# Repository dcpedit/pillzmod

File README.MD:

# Pillz Mod for the Kinesis Advantage/Contoured

This project replaces my two previous forks ([kinesismod](https://github.com/dcpedit/kinesismod) and [kint](https://github.com/dcpedit/kint)) for adding Blackpill support to the Kinesis keyboard.  I've decided to merge all the features into a single PCB, add optional thumb cluster PCBs as part of the kit, and renamed the project to avoid confusion.  Below is a list of supported features.

* Supports Blackpill development board running QMK/Vial
* Supports Pill Bug wireless Bluetooth development board running ZMK
* Optional reversible thumb cluster PCB for left/right sides.  (Maintains original matrix wiring)
* 2u stabilizer support on thumb cluster

## "Pro" PCB Features

* Supports devlopment board with Pro-Micro footprint (Elite-C, Elite-Pi, Nice!Nano)
* Header for connecting up to 3 foot-pedals
* Piezo audio buzzer
* Header for extra data pin (Elite-C only)

## Attribution

Credit goes to the following people for doing all the initial development on replacment PCBs for the Kinesis:
 * Aaron Silman's [kinesismod project](https://gitlab.com/Silman/kinesismod.git) ([blog](https://silman.io/project/kinesis_mod/))
 * Michael Stapelberg's [KinT project](https://github.com/kinx-project/kint) ([blog](https://michael.stapelberg.ch/posts/2020-07-09-kint-kinesis-keyboard-controller/))
 * Dmitry Nosachev's [Kin80 project](https://github.com/DmNosachev/kin80)

## Ordering PCBs from JLCPCB

The files needed for https://jlcpcb.com are located in the production folders:
* Choose `pcb-pro/production` or `pcb/production` 
* `thumb-pcb/production`

Once uploaded, you place the order with the selected default options.  You can optionally change the solder mask color, which changes the final color of your PCB.

## Main PCB build guide
### Components
| Position | Description | Qty | Notes |
| -------- | ----------- | --- | ----- |
| J1-J4    | Molex 39-53-2135 | 2 - 6  | [Link](https://octopart.com/39-53-2135-molex-7670149?r=sp)
| J3-J4    | Molex 39-53-2134 | 0 - 2  | Contoured only, [Link](https://octopart.com/search?q=Molex+39-53-2134)
| U1       | Header pins (1x20) | 2 | Should come with dev board
| U1       | Headers (1x20) | 2 | To socket your dev board
| D1-D4    | 1.8mm LED | 4 | [Amazon](https://a.co/d/90uynIs)
| R1-R4    | 10k resistor | 4 | Affects LED brightness. Smaller = brighter |
|          | USB-C panel mount | 1 | [AliExpress](https://www.aliexpress.us/item/3256806463941289.html?spm=a2g0o.order_list.order_list_main.43.18a31802pDYB6d&gatewayAdapt=glo2usa), [Amazon](https://a.co/d/cRoqHqx)

### Blackpill Components
| Position | Description | Qty | Notes |
| -------- | ----------- | --- | ----- |
| U1       | Blackpill (STM32F411) | 1 | [WeAct Store](https://www.aliexpress.com/store/1101545918?spm=a2g0o.order_list.order_list_main.2.18a31802pDYB6d)

#### -or- Pill Bug for wireless build

| Description | Qty | Notes |
| ----------- | --- | ----- |
| Pill Bug | 1 | [MechWild Store](https://mechwild.com/product/pillbug/)
| 3.7V battery | 1 | [2000mAh](https://a.co/d/dVUdHxi)
| Power button | 1 | Optional, [10mm](https://a.co/d/i33uBM0) or [19mm](https://a.co/d/fYN6ZX5)

### Additional "Pro" Components

| Position | Description | Qty | Notes |
| -------- | ----------- | --- | ----- |
| U1       | Elite-C/Elite-Pi | 1 |
|          | 3.7V battery | 1 | [2000mAh](https://a.co/d/dVUdHxi)
| U2       | 74HC595      | 1 | [Amazon](https://a.co/d/eLX9kOY)
| U2       | 16-pin IC socket | 1 | [Amazon](https://a.co/d/5EaFAHo)
| D6-D8    | 1n4148 Diode | 3 | [Link](https://www.mouser.com/ProductDetail/512-1N4148TR)
| BZ1      | Piezo Buzzer | 1 | [Link](https://www.digikey.com/en/products/detail/tdk-corporation/PS1240P02BT/935924)
| SW1      | Reset button | 1 | [Link](https://www2.mouser.com/ProductDetail/Alps-Alpine/SKQGAEE010?qs=N5Jky1br14PyTRvcw7F3eQ%3D%3D)
| R5-R19   | 10k Resistor | 15| AVR/Elite-C Only [Link](https://www.mouser.com/ProductDetail/YAGEO/MFR-12FTF52-10K?qs=oAGoVhmvjhzLlUYKKBtdYQ%3D%3D), [Link](https://mou.sr/3xgqcNf)

#### -or- Nice!Nano for wireless build

| Description | Qty | Notes |
| ----------- | --- | ----- |
| Nice!Nano    | 1 | [Website](https://nicekeyboards.com/nice-nano/)
| 3.7V battery | 1 | [2000mAh](https://a.co/d/dVUdHxi)
| Power button | 1 | Optional, [10mm](https://a.co/d/i33uBM0) or [19mm](https://a.co/d/fYN6ZX5)

### Instructions

_NOTE: If you're using a battery that's larger than 500mAh, then bridge the charge boost jumper labeled JP1 with some solder.  This will increases the max charge rate from 100mA to 500mA. Doing this for small batteries (<500mAh) may cause explosions._

All components go on the side with the silkscreen labels (rectangles) EXCEPT for the LEDs.  First solder the header pins onto your development board, and the header sockets onto the PCB.  I prefer to use Mill-Max 310 series sockets because the pins are thin.  Then solder in the LED resistors, but NOT the actual LEDs yet.  The resistors can be SMD or through hole.

For a wireless build, you can now solder the battery wires/connector to the board.  Make sure the positive wire goes into "BAT+", and the negative wire goes into "BAT-".  If you're using a power button, make sure to wire it inline along the BAT+ wire so that it essentially opens and closes the circuit.

Insert your development board into the sockets on the PCB.

For the Molex connectors, I find that it's more convient to desolder the ones on the original PCB so that I don't have to purchase new ones.  Solder the connectors onto the PCB.

Flip the PCB over and insert the LEDs on the side of the PCB with no other components.  Make sure the short leg goes into the square pad, and bend the legs so that they stay in place.  Screw the PCB back into the keyboard case, making sure the LEDs are lined up with the existing case holes.  You can also adjust the height of the LED to move them closer to the status window if you'd like.  Once you're satisfied with the position of the LEDs, you can then solder them in place while the PCB is still mounted.

Lastly, plug the USB-C panel mount cable to into the development board, and secure the other end to the hole in the case.

### "Pro" Additional Instructions

The components required for this build and their position will depend on the development board you're using.  For example, pull-down resistors R5-R19 are only needed for AVR chips (Pro-Micro, Elite-C) since they don't support internal pull-downs for the row inputs.  Use the image below as a guide.

The Elite-C has an extra B0 pin that is broken out into the J10 pins.  You can use this to drive other components if you choose (ie. RGB strip, Solenoid)

* Pin 1 (square pad) - VCC
* Pin 2 - B0
* Pin 3 - GND

The J9 pins are for foot pedals and have the following assignment:

* Pin 1 (square pad) - Col6
* Pin 2 - Row0
* Pin 3 - Row1
* Pin 4 - Row2

Diodes D6-D8 are connected to the rows, so no additional diodes are needed in the pedals/switches.

### "Pro" Nice!Nano Additional Instructions

Mill-Max 310 sockets are recommended for socketing the Nice!Nano because thin pins are required for connecting the extra 3 pins in the middle.

The Nice!Nano is one pin short of supporting all 4 status lights on the Advantage.  If you want to utilize the unused numpad status LED as a power indicator, go ahead and short JP1 with some solder.

## Thumb cluster PCB build guide

The wiring for the thumb cluster (a.k.a. matrix wiring) has not been altered from original, so theoretically, they can be used in conjunction with any Kinesis PCB, including the stock one.

The PCB is also reversible, so you don't have to place separate orders for a "left" version and a "right" version.

### Components

| Description | Qty | Notes |
| ----------- | --- | ----- |
| 1N4148 SOD-123 diode | 12 | [Amazon](https://a.co/d/gsv8bGT)
| MX switch | 12 | Can desolder and reuse
| 2u screw-in stabilizer | 4 | [Link](https://divinikey.com/products/durock-v2-stabilizers-screw-in)
| Cable connector (1x10) | 4 | 2.54mm pitch (eg KF2510)
| Ribbon cable | 2 | >= 50mm length

### Instructions

You will need two PCBs for the thumb cluster, but since they're reversible, you will need to read the silkscreen to see if it's the left or right cluster.

First step is to solder all the 1N4148 diodes.  Orientation matters, so make sure the line on the diode faces same direction as the thicker white line on the PCB.  Place a dab of solder on ONE of the two diode pads.  Drop the diode into position (double checking the orientation), hold the diode in place with tweezers, and melt the solder you just added to the pad so that diode is held in place.  Now add solder to the opposite pad, thus holding the other diode leg in place.  Repeat for all the other diodes.

The connector for the ribbon cable can now be soldered onto the PCB, and will be on the same side as the diodes.  The pin pitch is 2.54mm, so any compatible connector/cable will work here.

Install the 2u stabilizers onto the PCB.

Now solder in your MX switches.  If you're reusing the original switches, desolder them from the original PCB, and remove the diode from inside the switch housing.  Using a switch opener will make this task much easier.

Mount the thumb clusters onto the keyboard and connect the ribbon cables.

## QMK firmware for "Pro"

* `firmware/pro_qmk_avr_default.bin`
* `firmware/pro_qmk_rp2040_default.uf2`

QMK source: https://github.com/dcpedit/qmk_firmware/tree/pillzmod/keyboards/dcpedit/pillzmod

## Vial firmware for Blackpill

* `firmware/blackpill_vial.bin`
* `firmware/dcpedit_kint_bp_vial_6layers.bin`

Source: https://github.com/dcpedit/vial-qmk/tree/pillzmod/keyboards/dcpedit/pillzmod

Remap keys: https://vial.rocks/

### Flashing firmware under Linux
The file firmware/dcpedit_kint_bp_vial_6layers.bin (or other) can simply be flashed to the Blackpill using the dfu-util. The dfu-util tool requires root privileges if settings are not accessible by the user.

Connect Blackpill to your Linux PC via USB C cable and start unit in DFU mode by holding bootp button and pressing reset button. Wait a second and release the bootp button.

Check the DFU devices by running
```
dfu-util -l
```
The Blackpill device should be visible.

Write the firmware to the device with
```
dfu-util -d 0483:df11 -a 0 -s 0x08000000 -D [PATH TO kint]/firmware/dcpedit_kint_bp_vial_6layers.bin
```

## Vial firmware for "Pro"

* `firmware/pro_vial_avr.hex`

Source: https://github.com/dcpedit/vial-qmk/tree/pillzmod/keyboards/dcpedit/pillzmod
(You will need to clone the entire branch since I had to make a core code change in `spi_master.c`)

## ZMK firmware for Pill Bug

* `firmware/zmk_default.uf2` - Default keymap
* `firmware/zmk_custom.uf2` - Support for up to 6 layers
* `firmware/zmk_reset.uf2` - Resets PillBug board for BT connectivity issue on MacOS      
* `firmware/zmk_studio.uf2` - Studio compatible (Progrm + Esc to unlock)

Source: https://github.com/dcpedit/zmk/tree/pillzmod/app/boards/shields/pillzmod

### Bluetooth with ZMK

The ZMK firmware has mappings for performing system tasks. By default there are 4 Bluetooth pairings saved to the keyboard but they do not switch automatically when adding new devices. So after you add the first device, you need to tell they keyboard to use Bluetooth slot 2 and so forth.
The keys to switch between are accessed by a different keyboard layer. This layer is opened by holding down the "Program" key at the very top right of the Kinesis and, while holding it, then clicking another key as follows:

* **Clear all saved Bluetooth profiles:** Program + F9
* **Bluetooth profile 1:** Program + F1
* **Bluetooth profile 2:** Program + F2
* **Bluetooth profile 3:** Program + F3
* **Bluetooth profile 4:** Program + F4
* **Enter bootloader mode (to upload UF2 files):** Program + - (the dash key just below program)

If you want to do a ZMK firmware build using GitHub actions, take a look at the following repository from keepitsimplejim:

https://github.com/keepitsimplejim/zmk-config-pillzmod-kinesis-adv

## ZMK firmware for "Pro" Nice!Nano

* `firmware/pro_zmk.uf2` - Default keymap
* `firmware/pro_zmk_studio.uf2` - Studio compatible (Progrm + Esc to unlock)

Source: https://github.com/dcpedit/zmk/tree/pillzmod/app/boards/shields/pillzmod_pro
Studio: https://zmk.studio/

## KiCad

All the PCBs were designed using KiCad, which is free and can be downloaded here: https://www.kicad.org/

For the thumb cluster PCB, I wasn't able to figure out how to have the left and right wiring co-exist without errors while sharing the same connector footprint.  My workaround was to first change the connector's reference designator to "J1", update the PCB from schematic, and wire up the left side.  Then I changed the reference designator to "J2", updated the PCB from schematic again, and wired up the right side.

If there are any KiCad experts out there that know of a more elegant solution, please let me know.

The production JLCPCB files are all generated with Fabrication Toolkit: https://github.com/bennymeg/Fabrication-Toolkit

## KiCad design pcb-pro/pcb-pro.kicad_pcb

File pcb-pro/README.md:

# Pillz Mod Pro main PCB

Next image shows the mapping of keys to connectors and rows/columns:

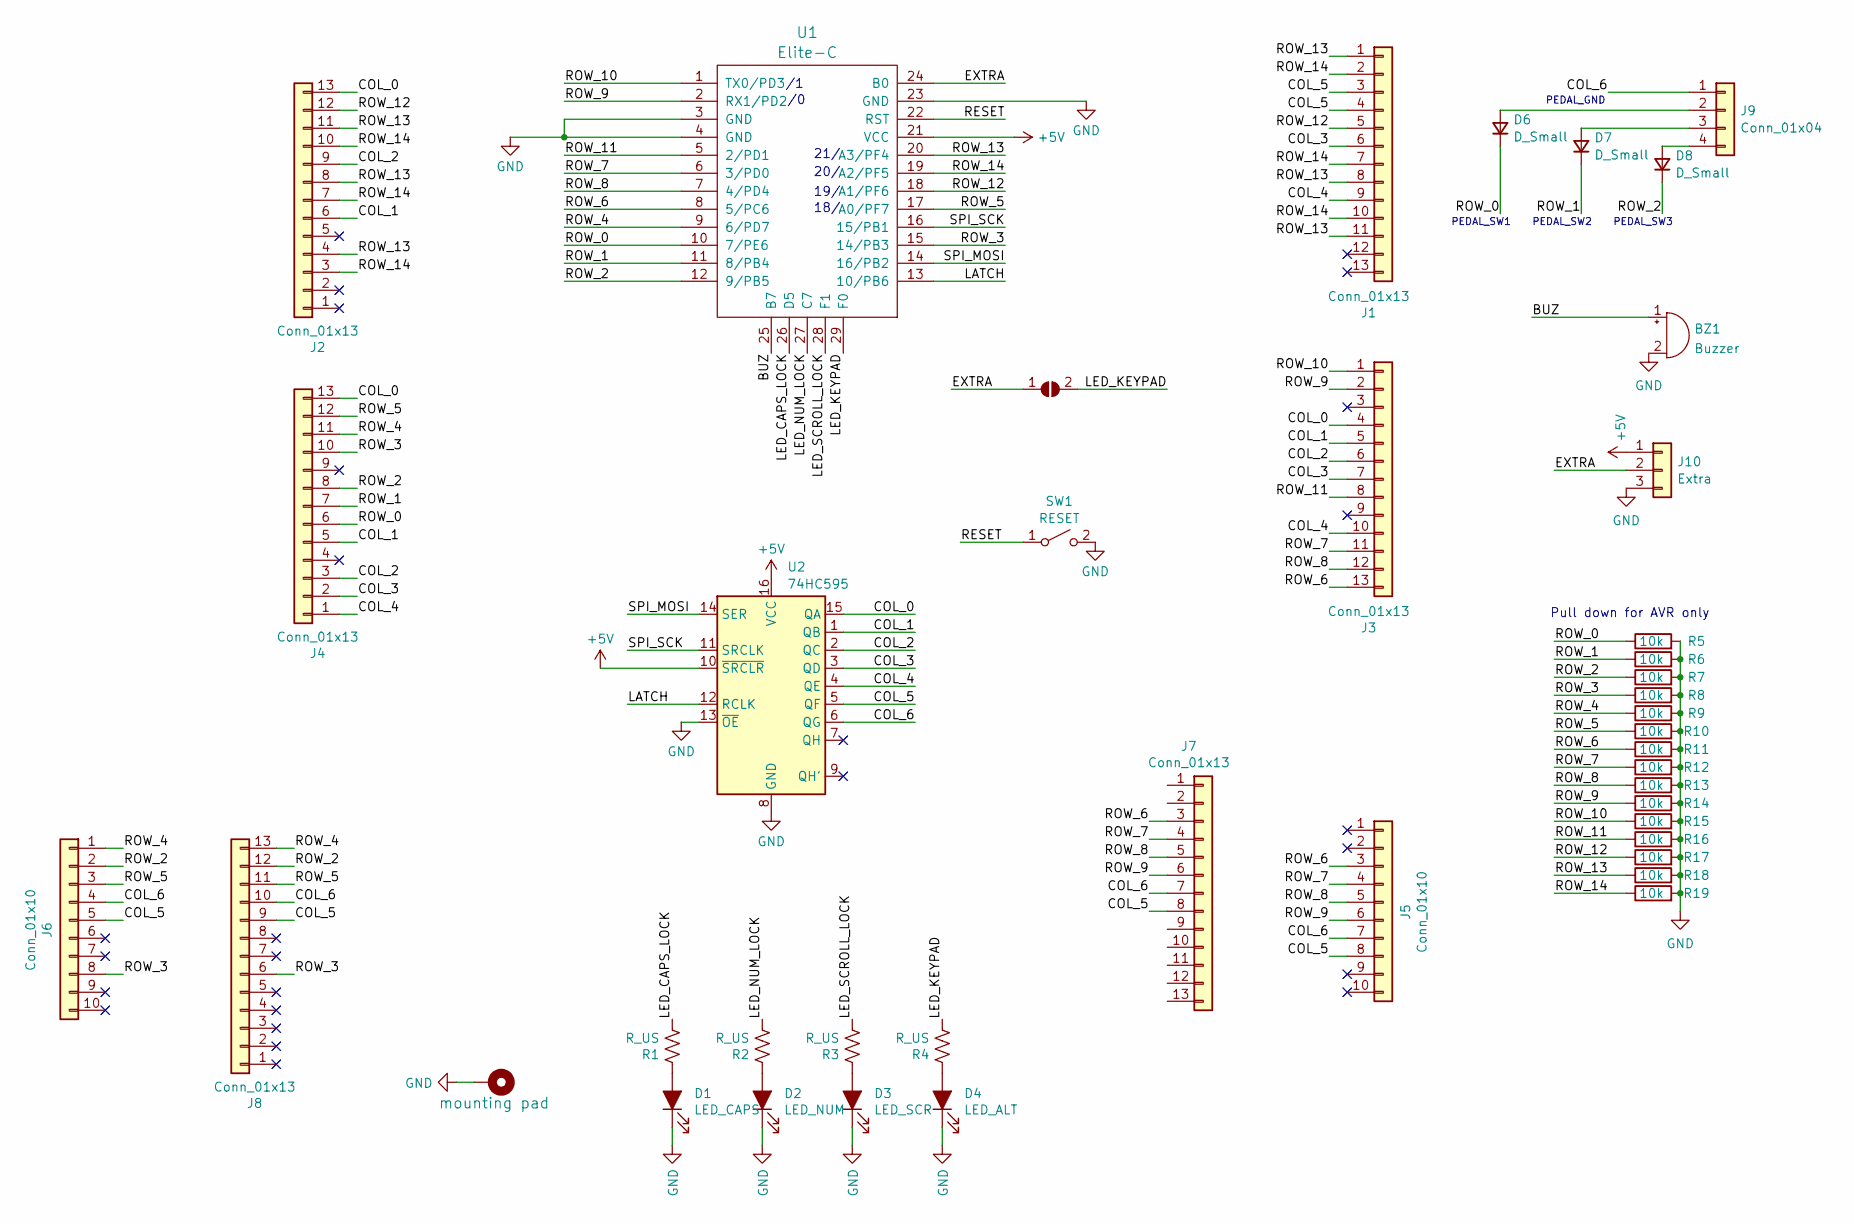
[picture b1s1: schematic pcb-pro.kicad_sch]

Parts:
BZ1: Buzzer
D1: LED_CAPS; LED_D3.0mm
D2: LED_NUM; LED_D3.0mm
D3: LED_SCR; LED_D3.0mm
D4: LED_ALT; LED_D3.0mm
D6, D7, D8: D_Small
H1: mounting pad; MountingHole_4.3mm_M4_Pad
J1, J2, J7, J8: Conn_01x13; Molex_0039532135
J3, J4: Conn_01x13; Molex_039532134
J5, J6: Conn_01x10; Pin_Header_Straight_1x10_Pitch2.54mm
J9: Conn_01x04
J10: Extra
JP1: SolderJumper_2_Open; SolderJumper-2_P1.3mm_Open_RoundedPad1.0x1.5mm
R1, R2, R3, R4: R_US; R_Axial_DIN0204_L3.6mm_D1.6mm_P5.08mm_Horizontal
R5, R6, R7, R8, R9, R10, R11, R12, R13, R14, R15, R16, R17, R18, R19: 10k
SW1: RESET
U1: Elite-C
U2: 74HC595

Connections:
+5V: J10.1, U1.21 (VCC), U2.10 (~SRCLR), U2.16 (VCC)
/BUZ: BZ1.1 (-), U1.25 (B7)
/COL_0: J2.13, J3.4, J4.13, U2.15 (QA)
/COL_1: J2.6, J3.5, J4.5, U2.1 (QB)
/COL_2: J2.9, J3.6, J4.3, U2.2 (QC)
/COL_3: J1.6, J3.7, J4.2, U2.3 (QD)
/COL_4: J1.9, J3.10, J4.1, U2.4 (QE)
/COL_5: J1.3, J1.4, J5.8, J6.5, J7.8, J8.9, U2.5 (QF)
/COL_6: J5.7, J6.4, J7.7, J8.10, J9.1, U2.6 (QG)
/EXTRA: J10.2, JP1.1 (A), U1.24 (B0)
/LATCH: U1.13 (10/PB6), U2.12 (RCLK)
/LED_CAPS_LOCK: R1.2, U1.26 (D5)
/LED_KEYPAD: JP1.2 (B), R4.2, U1.29 (F0)
/LED_NUM_LOCK: R2.2, U1.27 (C7)
/LED_SCROLL_LOCK: R3.2, U1.28 (F1)
/RESET: SW1.1 (A), U1.22 (RST)
/ROW_0: D6.1 (K), J4.6, R5.1, U1.10 (7/PE6)
/ROW_1: D7.1 (K), J4.7, R6.1, U1.11 (8/PB4)
/ROW_2: D8.1 (K), J4.8, J6.2, J8.12, R7.1, U1.12 (9/PB5)
/ROW_3: J4.10, J6.8, J8.6, R8.1, U1.15 (14/PB3)
/ROW_4: J4.11, J6.1, J8.13, R9.1, U1.9 (6/PD7)
/ROW_5: J4.12, J6.3, J8.11, R10.1, U1.17 (A0/PF7)
/ROW_6: J3.13, J5.3, J7.3, R11.1, U1.8 (5/PC6)
/ROW_7: J3.11, J5.4, J7.4, R12.1, U1.6 (3/PD0)
/ROW_8: J3.12, J5.5, J7.5, R13.1, U1.7 (4/PD4)
/ROW_9: J3.2, J5.6, J7.6, R14.1, U1.2 (RX1/PD2)
/ROW_10: J3.1, R15.1, U1.1 (TX0/PD3)
/ROW_11: J3.8, R16.1, U1.5 (2/PD1)
/ROW_12: J1.5, J2.12, R17.1, U1.18 (A1/PF6)
/ROW_13: J1.1, J1.8, J1.11, J2.4, J2.8, J2.11, R18.1, U1.20 (A3/PF4)
/ROW_14: J1.2, J1.7, J1.10, J2.3, J2.7, J2.10, R19.1, U1.19 (A2/PF5)
/SPI_MOSI: U1.14 (16/PB2), U2.14 (SER)
/SPI_SCK: U1.16 (15/PB1), U2.11 (SRCLK)
GND: BZ1.2 (+), D1.1 (K), D2.1 (K), D3.1 (K), D4.1 (K), H1.1, J10.3, R5.2, R6.2, R7.2, R8.2, R9.2, R10.2, R11.2, R12.2, R13.2, R14.2, R15.2, R16.2, R17.2, R18.2, R19.2, SW1.2 (B), U1.3 (GND), U1.4 (GND), U1.23 (GND), U2.8 (GND), U2.13 (~OE)
unnamed: D1.2 (A), R1.1
unnamed: D2.2 (A), R2.1
unnamed: D3.2 (A), R3.1
unnamed: D4.2 (A), R4.1
unnamed: D6.2 (A), J9.2
unnamed: D7.2 (A), J9.3
unnamed: D8.2 (A), J9.4

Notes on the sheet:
Pull down for AVR only
18/
PEDAL_SW3
19/
20/
PEDAL_SW1
21/
PEDAL_GND
PEDAL_SW2

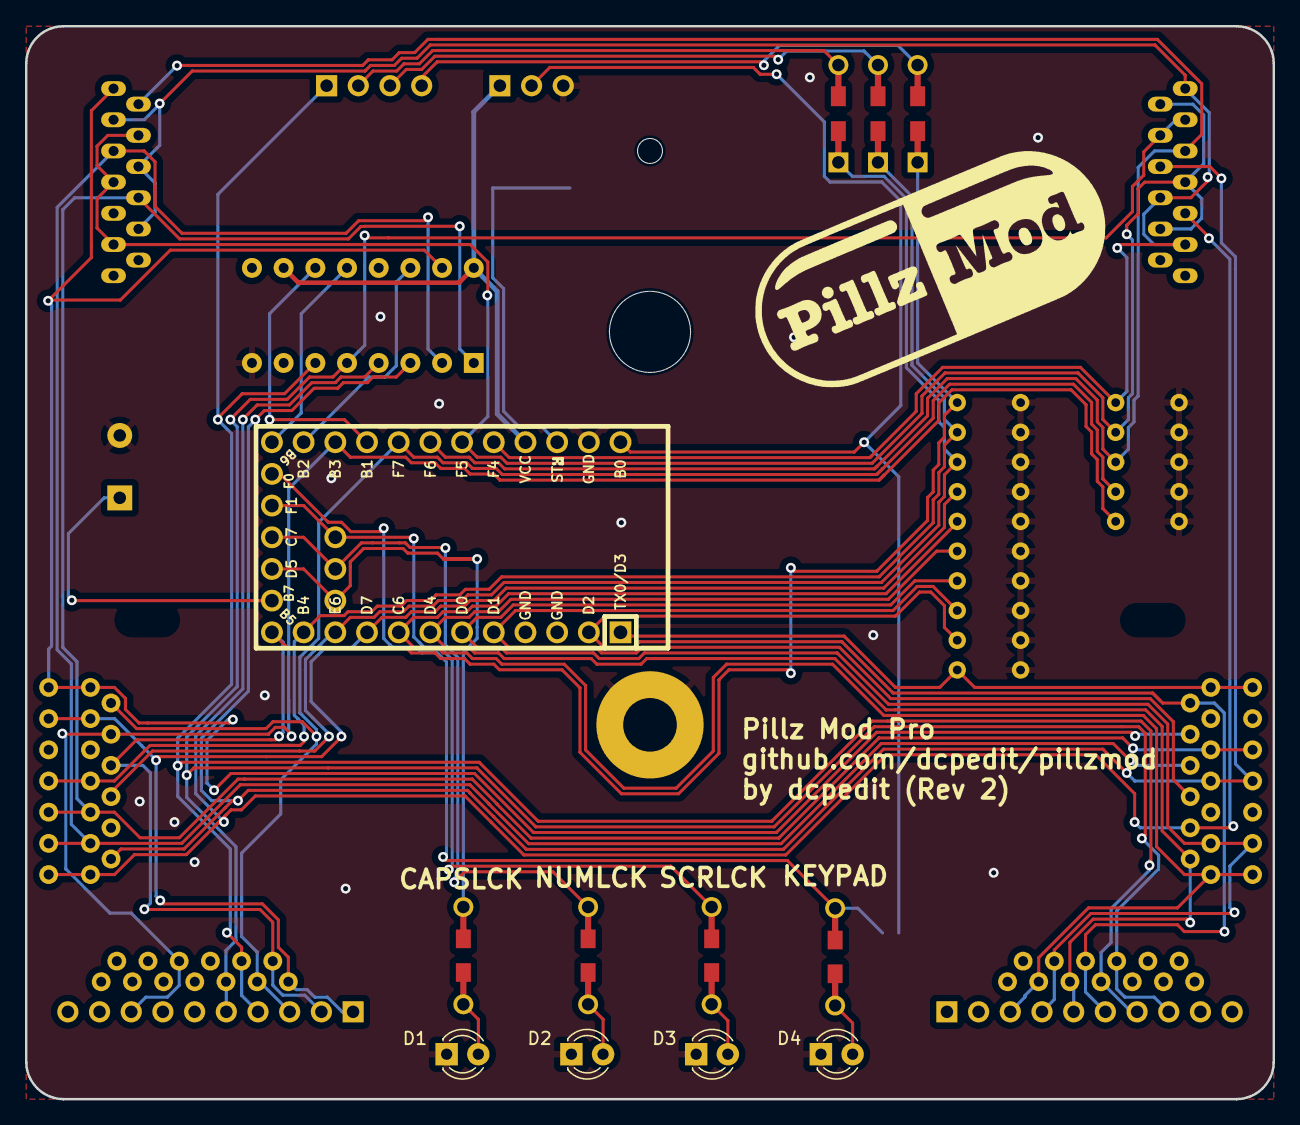
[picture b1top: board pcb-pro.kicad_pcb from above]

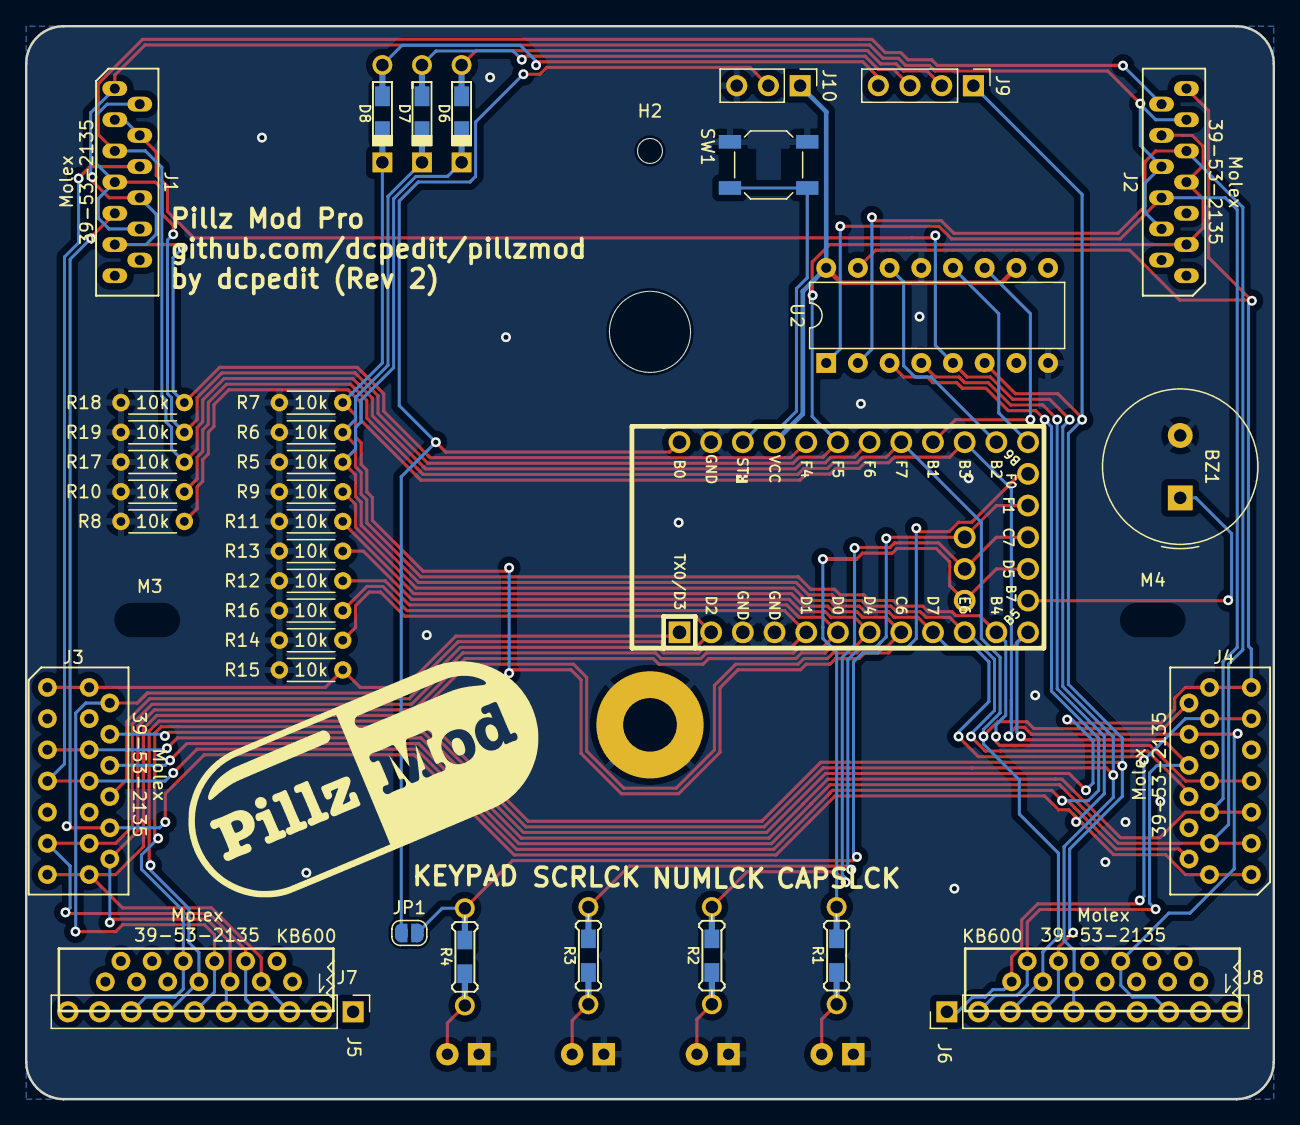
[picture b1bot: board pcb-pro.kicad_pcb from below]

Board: 2 copper layers, 100.0 x 86.0 mm, 46 parts (41 on the bottom side), 41 nets.

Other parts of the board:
H2: mounting pad; MountingHole_2mm
M1: MountingHole_6.4mm_M6
M3, M4: MountingHole_4.3mm_M4

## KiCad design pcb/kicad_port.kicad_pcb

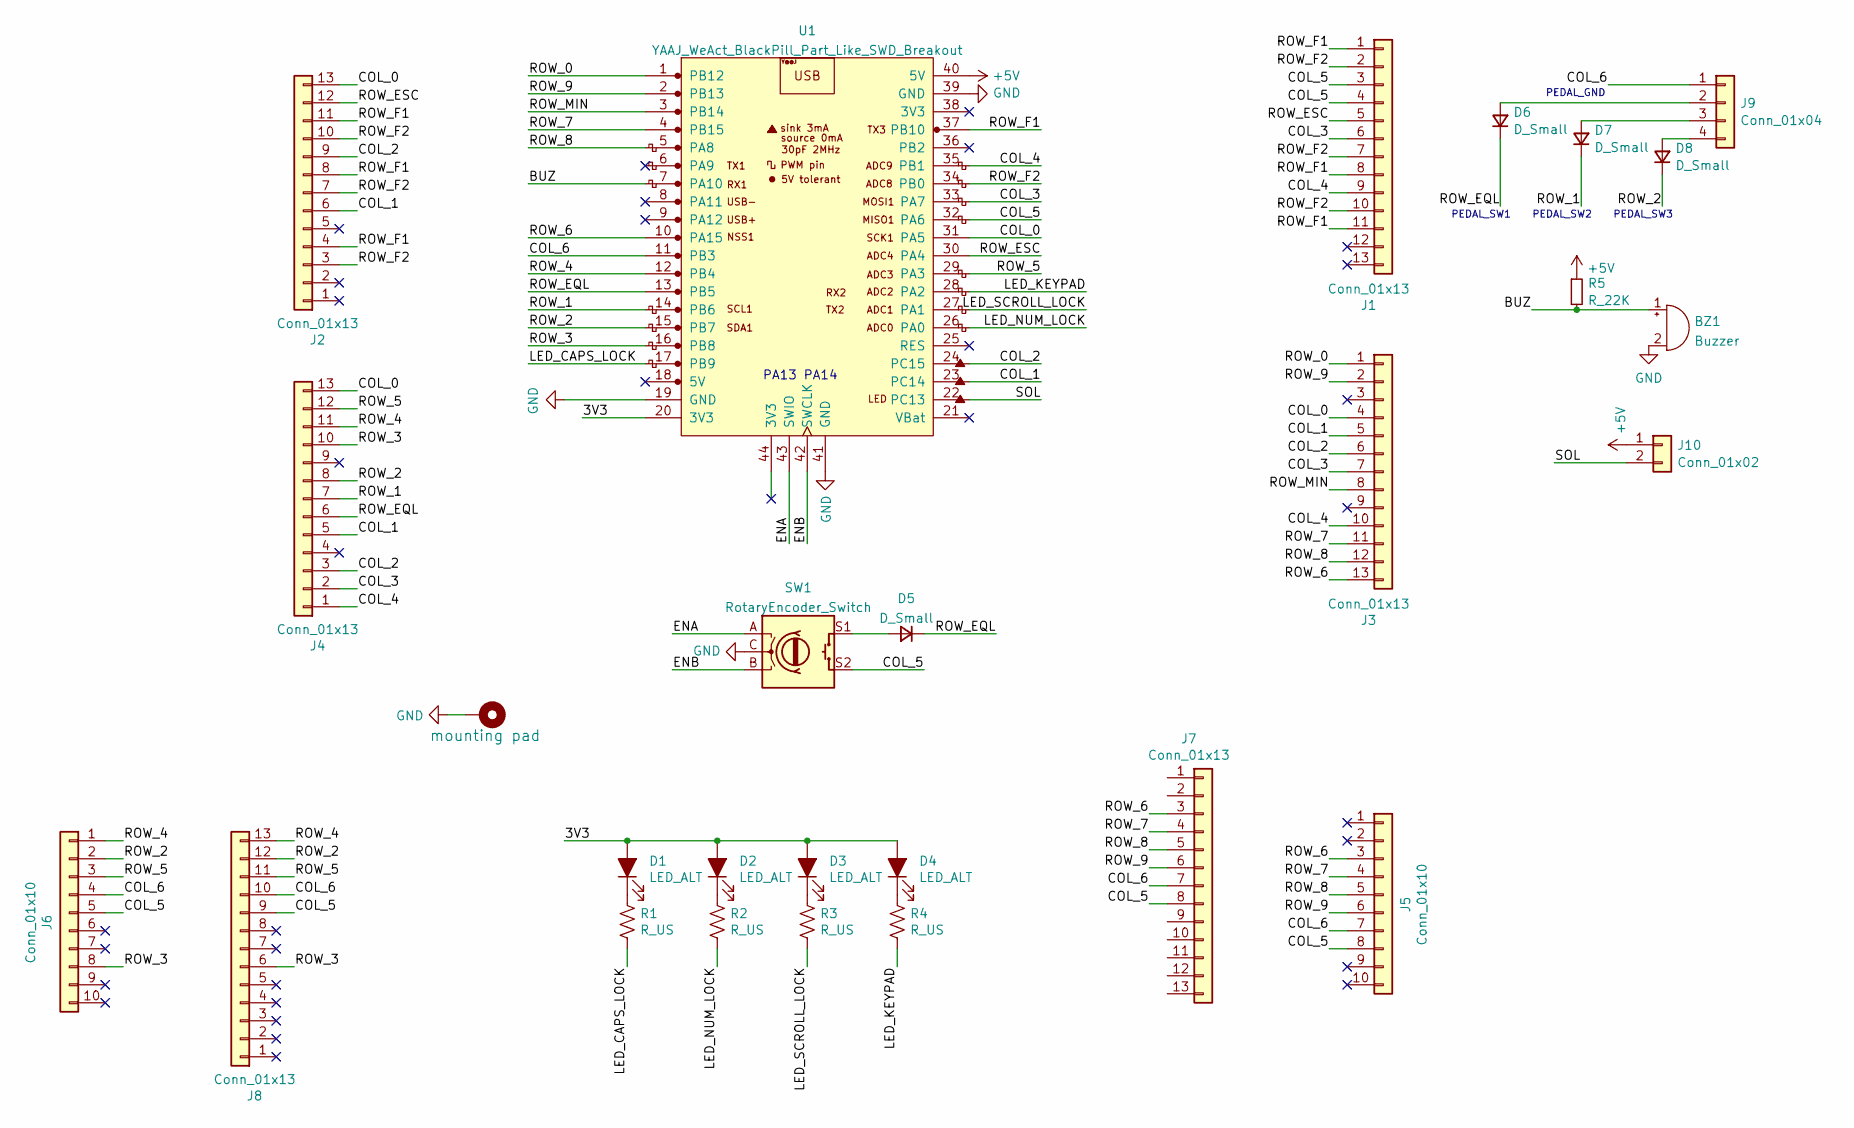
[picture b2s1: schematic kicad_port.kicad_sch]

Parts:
BZ1: Buzzer
D1, D2, D3, D4: LED_ALT; LED_D3.0mm
D5, D6, D7, D8: D_Small
H1: mounting pad; MountingHole_4.3mm_M4_Pad
J1, J2, J7, J8: Conn_01x13; Molex_0039532135
J3, J4: Conn_01x13; Molex_039532134
J5, J6: Conn_01x10; Pin_Header_Straight_1x10_Pitch2.54mm
J9: Conn_01x04
J10: Conn_01x02
R1, R2, R3, R4: R_US; R_Axial_DIN0204_L3.6mm_D1.6mm_P5.08mm_Horizontal
R5: R_22K; Resistor
SW1: RotaryEncoder_Switch
U1: YAAJ_WeAct_BlackPill_Part_Like_SWD_Breakout; YAAJ_WeAct_BlackPill_SWD_2

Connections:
+5V: J10.1, R5.1, U1.40 (5V)
/3V3: D1.2 (A), D2.2 (A), D3.2 (A), D4.2 (A), U1.20 (3V3)
/BUZ: BZ1.1 (-), R5.2, U1.7 (PA10)
/COL_0: J2.13, J3.4, J4.13, U1.31 (PA5)
/COL_1: J2.6, J3.5, J4.5, U1.23 (PC14)
/COL_2: J2.9, J3.6, J4.3, U1.24 (PC15)
/COL_3: J1.6, J3.7, J4.2, U1.33 (PA7)
/COL_4: J1.9, J3.10, J4.1, U1.35 (PB1)
/COL_5: J1.3, J1.4, J5.8, J6.5, J7.8, J8.9, SW1.S2, U1.32 (PA6)
/COL_6: J5.7, J6.4, J7.7, J8.10, J9.1, U1.11 (PB3)
/ENA: SW1.A, U1.43 (SWIO)
/ENB: SW1.B, U1.42 (SWCLK)
/LED_CAPS_LOCK: R1.2, U1.17 (PB9)
/LED_KEYPAD: R4.2, U1.28 (PA2)
/LED_NUM_LOCK: R2.2, U1.26 (PA0)
/LED_SCROLL_LOCK: R3.2, U1.27 (PA1)
/ROW_0: J3.1, U1.1 (PB12)
/ROW_1: D7.1 (K), J4.7, U1.14 (PB6)
/ROW_2: D8.1 (K), J4.8, J6.2, J8.12, U1.15 (PB7)
/ROW_3: J4.10, J6.8, J8.6, U1.16 (PB8)
/ROW_4: J4.11, J6.1, J8.13, U1.12 (PB4)
/ROW_5: J4.12, J6.3, J8.11, U1.29 (PA3)
/ROW_6: J3.13, J5.3, J7.3, U1.10 (PA15)
/ROW_7: J3.11, J5.4, J7.4, U1.4 (PB15)
/ROW_8: J3.12, J5.5, J7.5, U1.5 (PA8)
/ROW_9: J3.2, J5.6, J7.6, U1.2 (PB13)
/ROW_EQL: D5.1 (K), D6.1 (K), J4.6, U1.13 (PB5)
/ROW_ESC: J1.5, J2.12, U1.30 (PA4)
/ROW_F1: J1.1, J1.8, J1.11, J2.4, J2.8, J2.11, U1.37 (PB10)
/ROW_F2: J1.2, J1.7, J1.10, J2.3, J2.7, J2.10, U1.34 (PB0)
/ROW_MIN: J3.8, U1.3 (PB14)
/SOL: J10.2, U1.22 (PC13)
GND: BZ1.2 (+), H1.1, SW1.C, U1.19 (GND), U1.39 (GND), U1.41 (GND)
unnamed: D1.1 (K), R1.1
unnamed: D2.1 (K), R2.1
unnamed: D3.1 (K), R3.1
unnamed: D4.1 (K), R4.1
unnamed: D5.2 (A), SW1.S1
unnamed: D6.2 (A), J9.2
unnamed: D7.2 (A), J9.3
unnamed: D8.2 (A), J9.4

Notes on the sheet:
PA13 PA14
PEDAL_SW3
PEDAL_SW1
PEDAL_GND
PEDAL_SW2

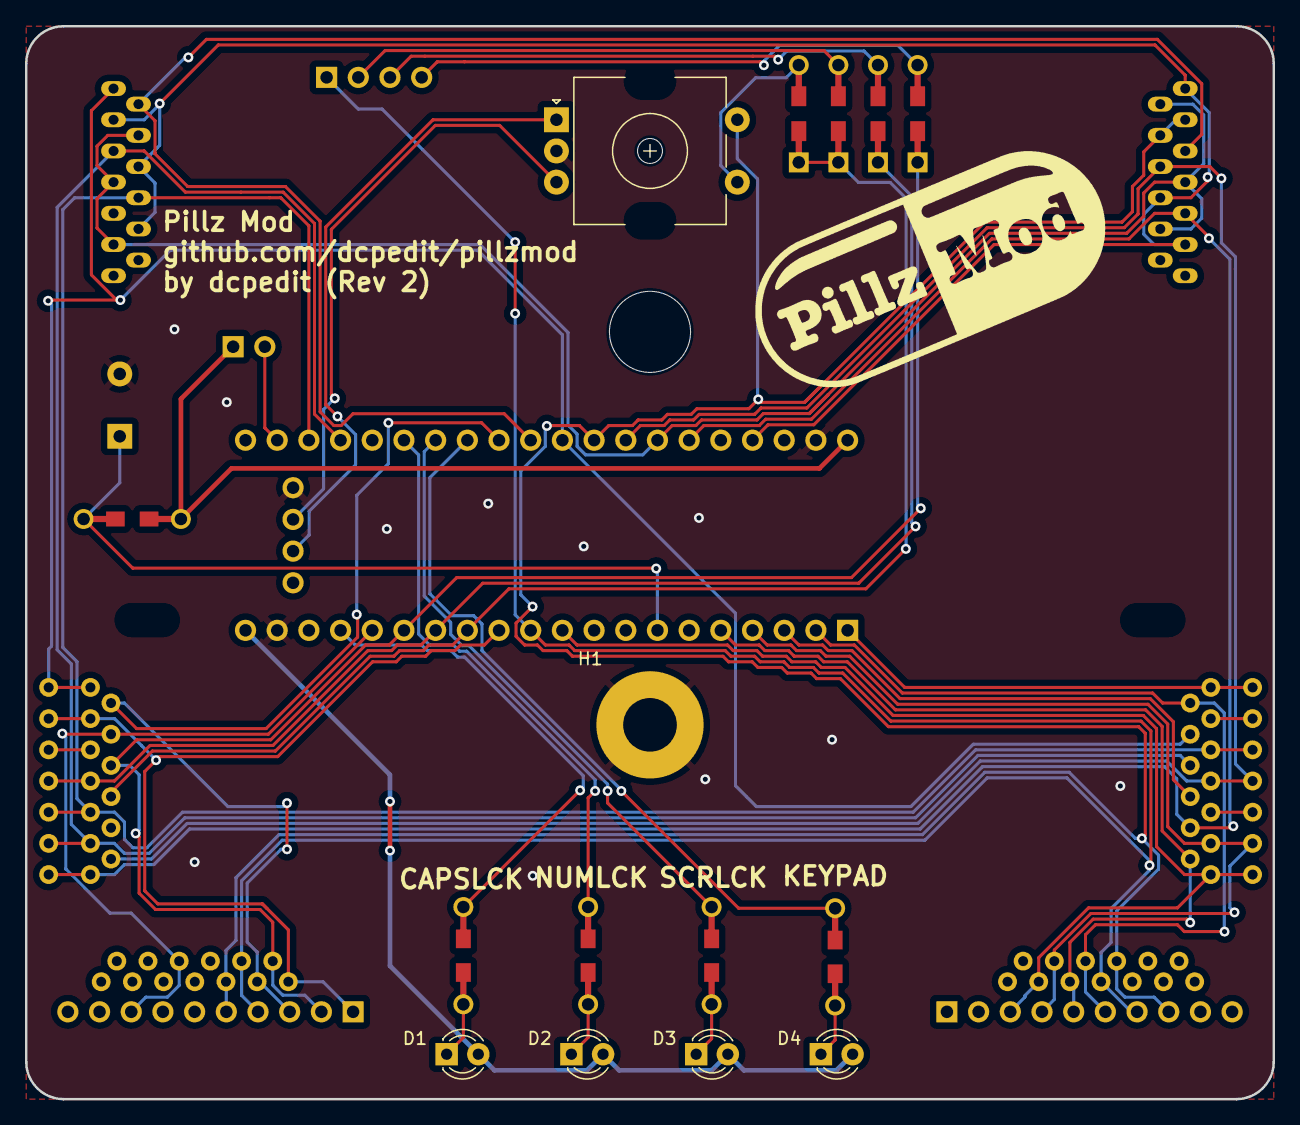
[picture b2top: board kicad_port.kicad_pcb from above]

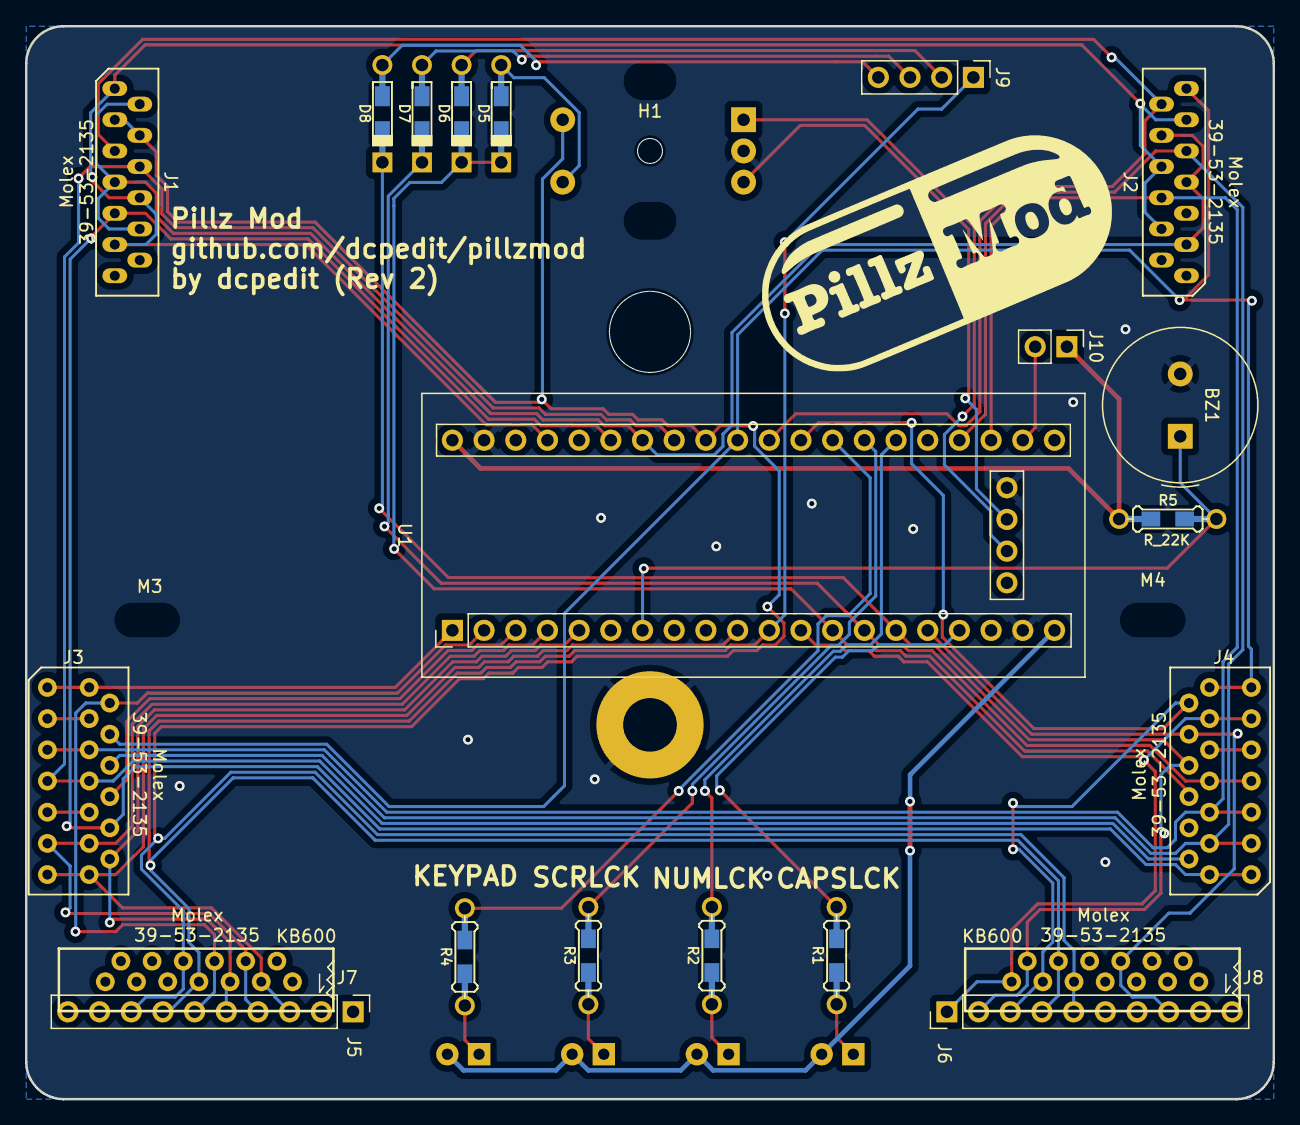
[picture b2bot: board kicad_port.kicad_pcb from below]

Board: 2 copper layers, 100.0 x 86.0 mm, 31 parts (25 on the bottom side), 41 nets.

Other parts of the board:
H1#2: mounting pad; MountingHole_2mm
M1: MountingHole_6.4mm_M6
M3, M4: MountingHole_4.3mm_M4

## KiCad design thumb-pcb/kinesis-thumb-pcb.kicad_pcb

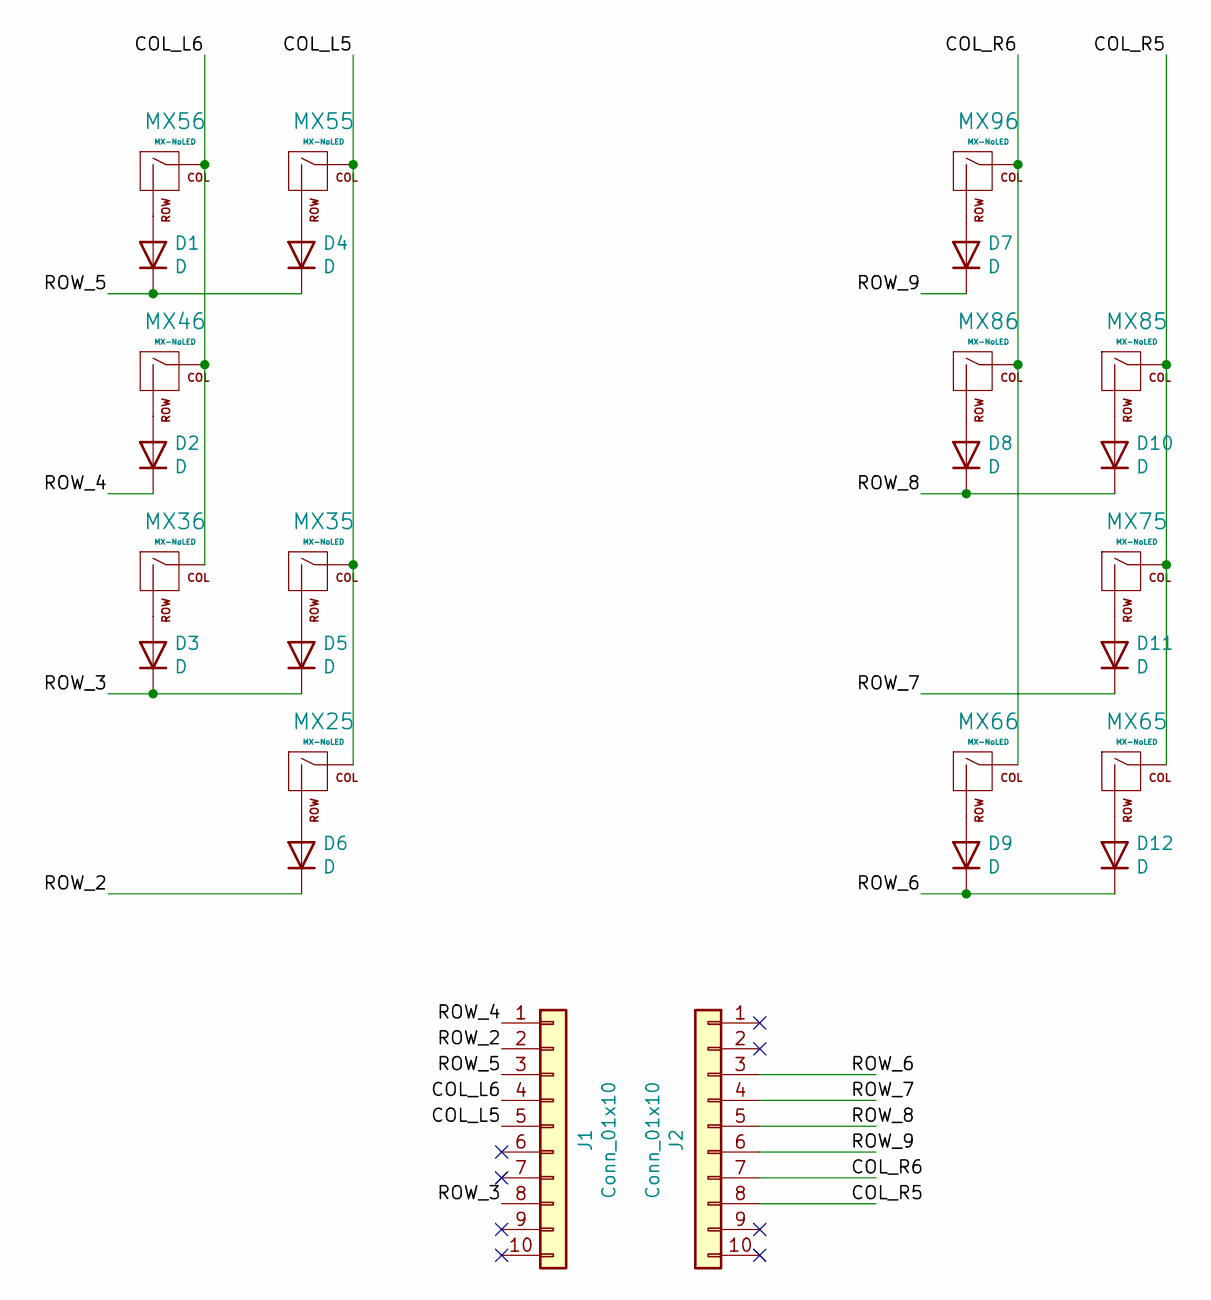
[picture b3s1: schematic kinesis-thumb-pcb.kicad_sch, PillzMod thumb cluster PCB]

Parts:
D1, D2, D3, D4, D5, D6, D7, D8, D9, D10, D11, D12: D; D_SOD-323_HandSoldering
J1, J2: Conn_01x10; Pin_Header_Straight_1x10_Pitch2.54mm
MX25, MX35, MX36, MX46, MX55, MX56, MX65, MX66, MX75, MX85, MX86, MX96: MX-NoLED

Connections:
/COL_L5: J1.5, MX25.1 (COL), MX35.1 (COL), MX55.1 (COL)
/COL_L6: J1.4, MX36.1 (COL), MX46.1 (COL), MX56.1 (COL)
/COL_R5: J2.8, MX65.1 (COL), MX75.1 (COL), MX85.1 (COL)
/COL_R6: J2.7, MX66.1 (COL), MX86.1 (COL), MX96.1 (COL)
/ROW_2: D6.1 (K), J1.2
/ROW_3: D3.1 (K), D5.1 (K), J1.8
/ROW_4: D2.1 (K), J1.1
/ROW_5: D1.1 (K), D4.1 (K), J1.3
/ROW_6: D9.1 (K), D12.1 (K), J2.3
/ROW_7: D11.1 (K), J2.4
/ROW_8: D8.1 (K), D10.1 (K), J2.5
/ROW_9: D7.1 (K), J2.6
unnamed: D1.2 (A), MX56.2 (ROW)
unnamed: D2.2 (A), MX46.2 (ROW)
unnamed: D3.2 (A), MX36.2 (ROW)
unnamed: D4.2 (A), MX55.2 (ROW)
unnamed: D5.2 (A), MX35.2 (ROW)
unnamed: D6.2 (A), MX25.2 (ROW)
unnamed: D7.2 (A), MX96.2 (ROW)
unnamed: D8.2 (A), MX86.2 (ROW)
unnamed: D9.2 (A), MX66.2 (ROW)
unnamed: D10.2 (A), MX85.2 (ROW)
unnamed: D11.2 (A), MX75.2 (ROW)
unnamed: D12.2 (A), MX65.2 (ROW)

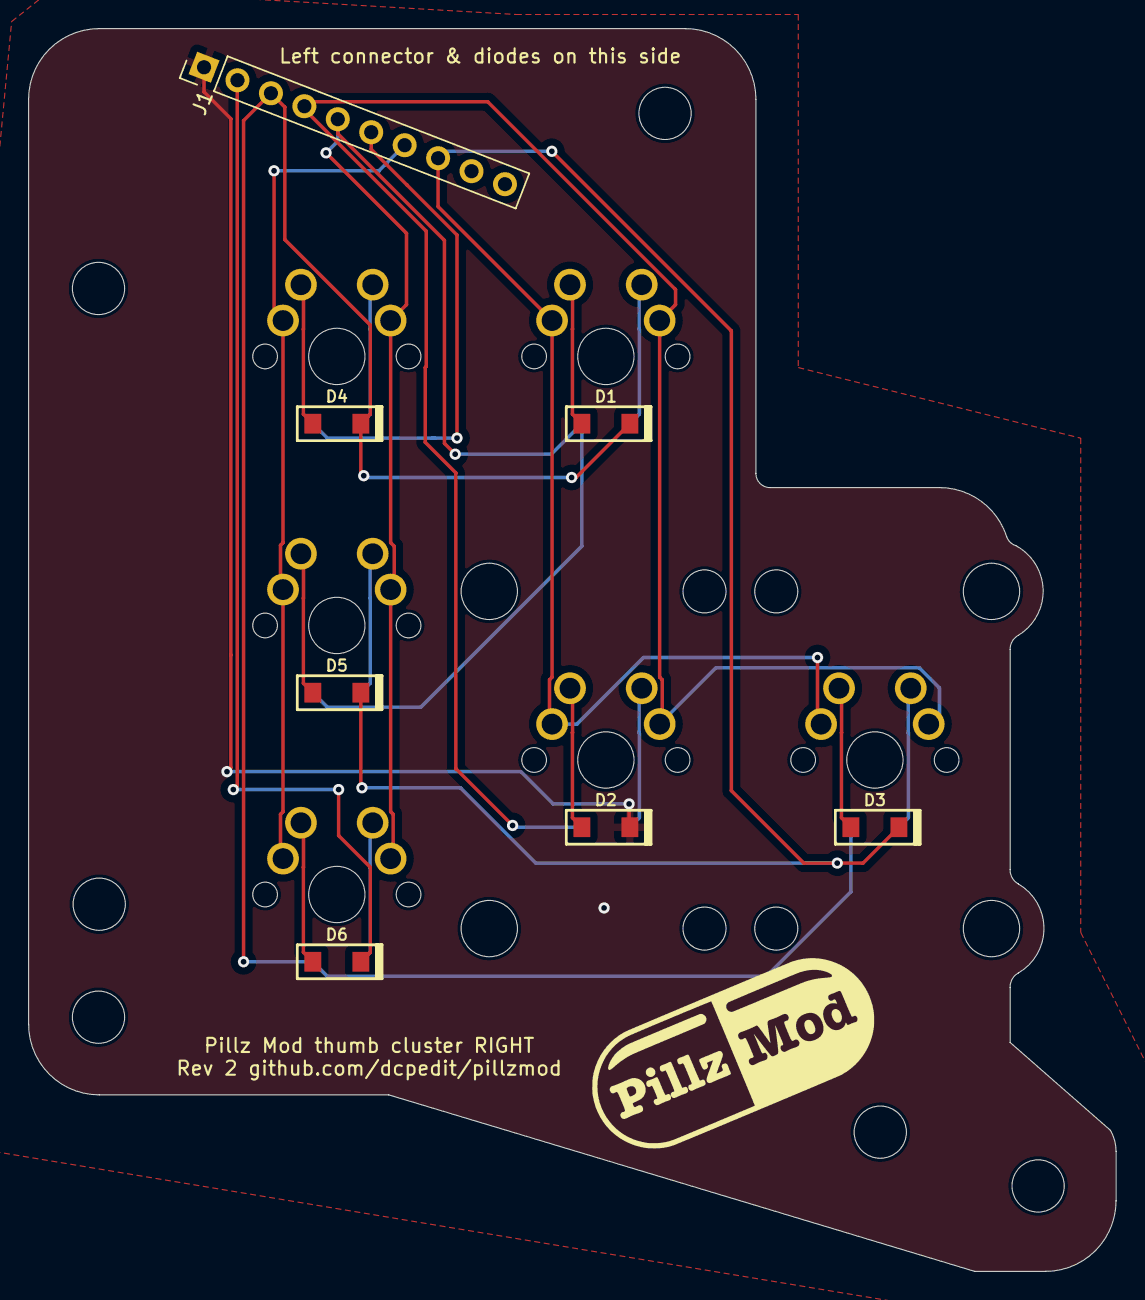
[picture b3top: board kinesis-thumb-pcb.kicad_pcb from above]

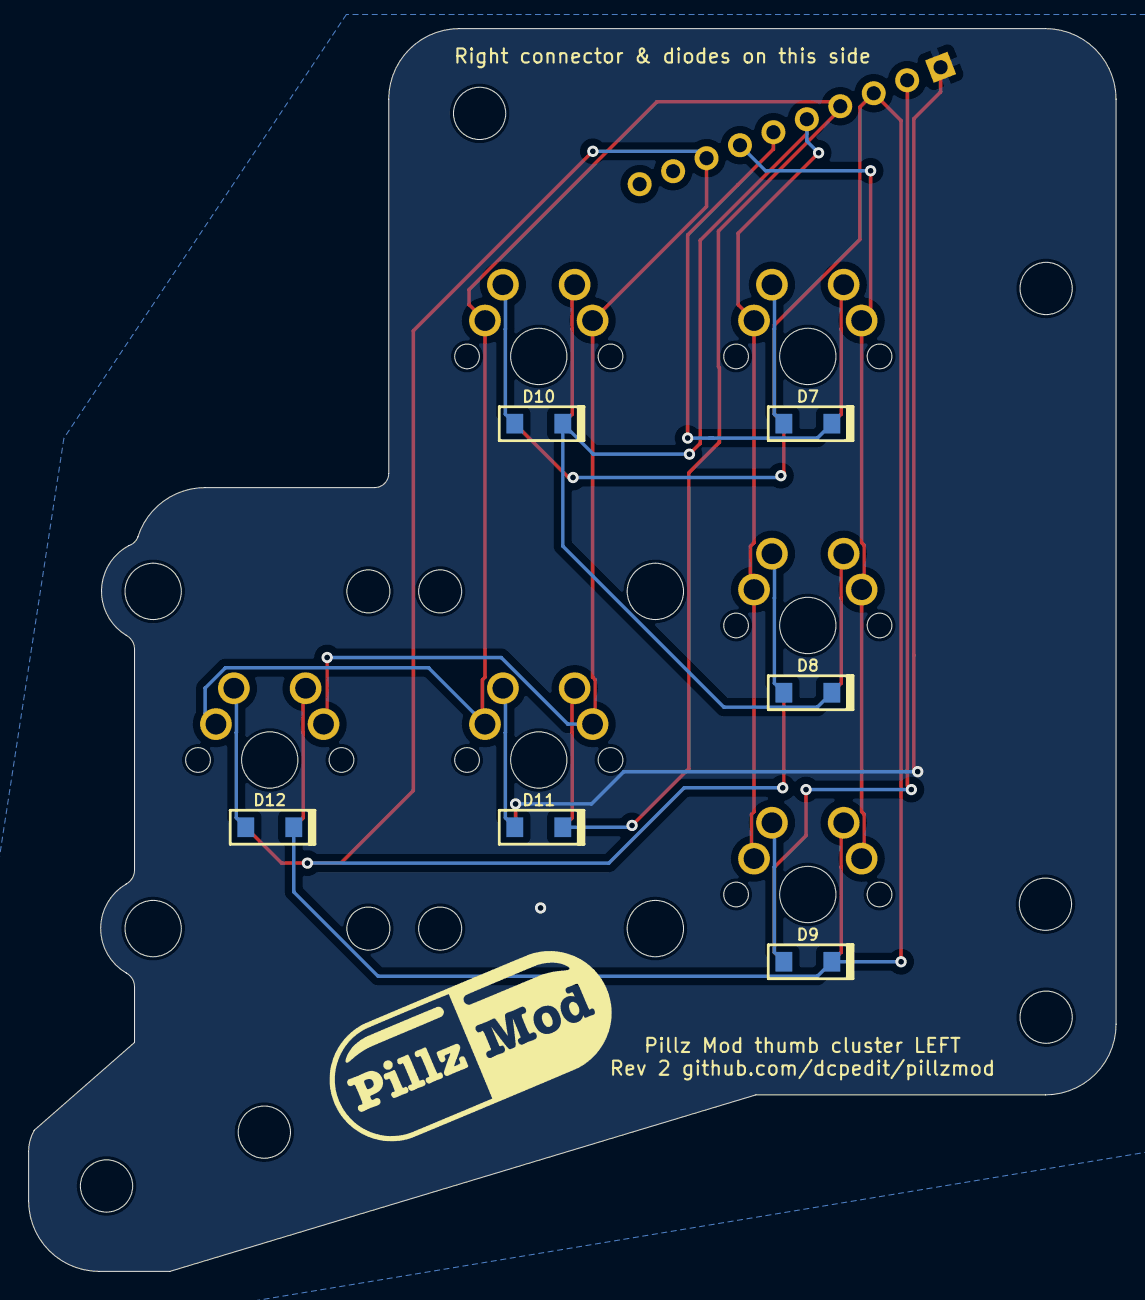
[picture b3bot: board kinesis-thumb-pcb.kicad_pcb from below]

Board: 2 copper layers, 77.0 x 88.0 mm, 31 parts (18 on the bottom side), 22 nets.

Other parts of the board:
REF1, REF2, REF3, REF4, REF5, REF6: MountingHole_3.7mm
